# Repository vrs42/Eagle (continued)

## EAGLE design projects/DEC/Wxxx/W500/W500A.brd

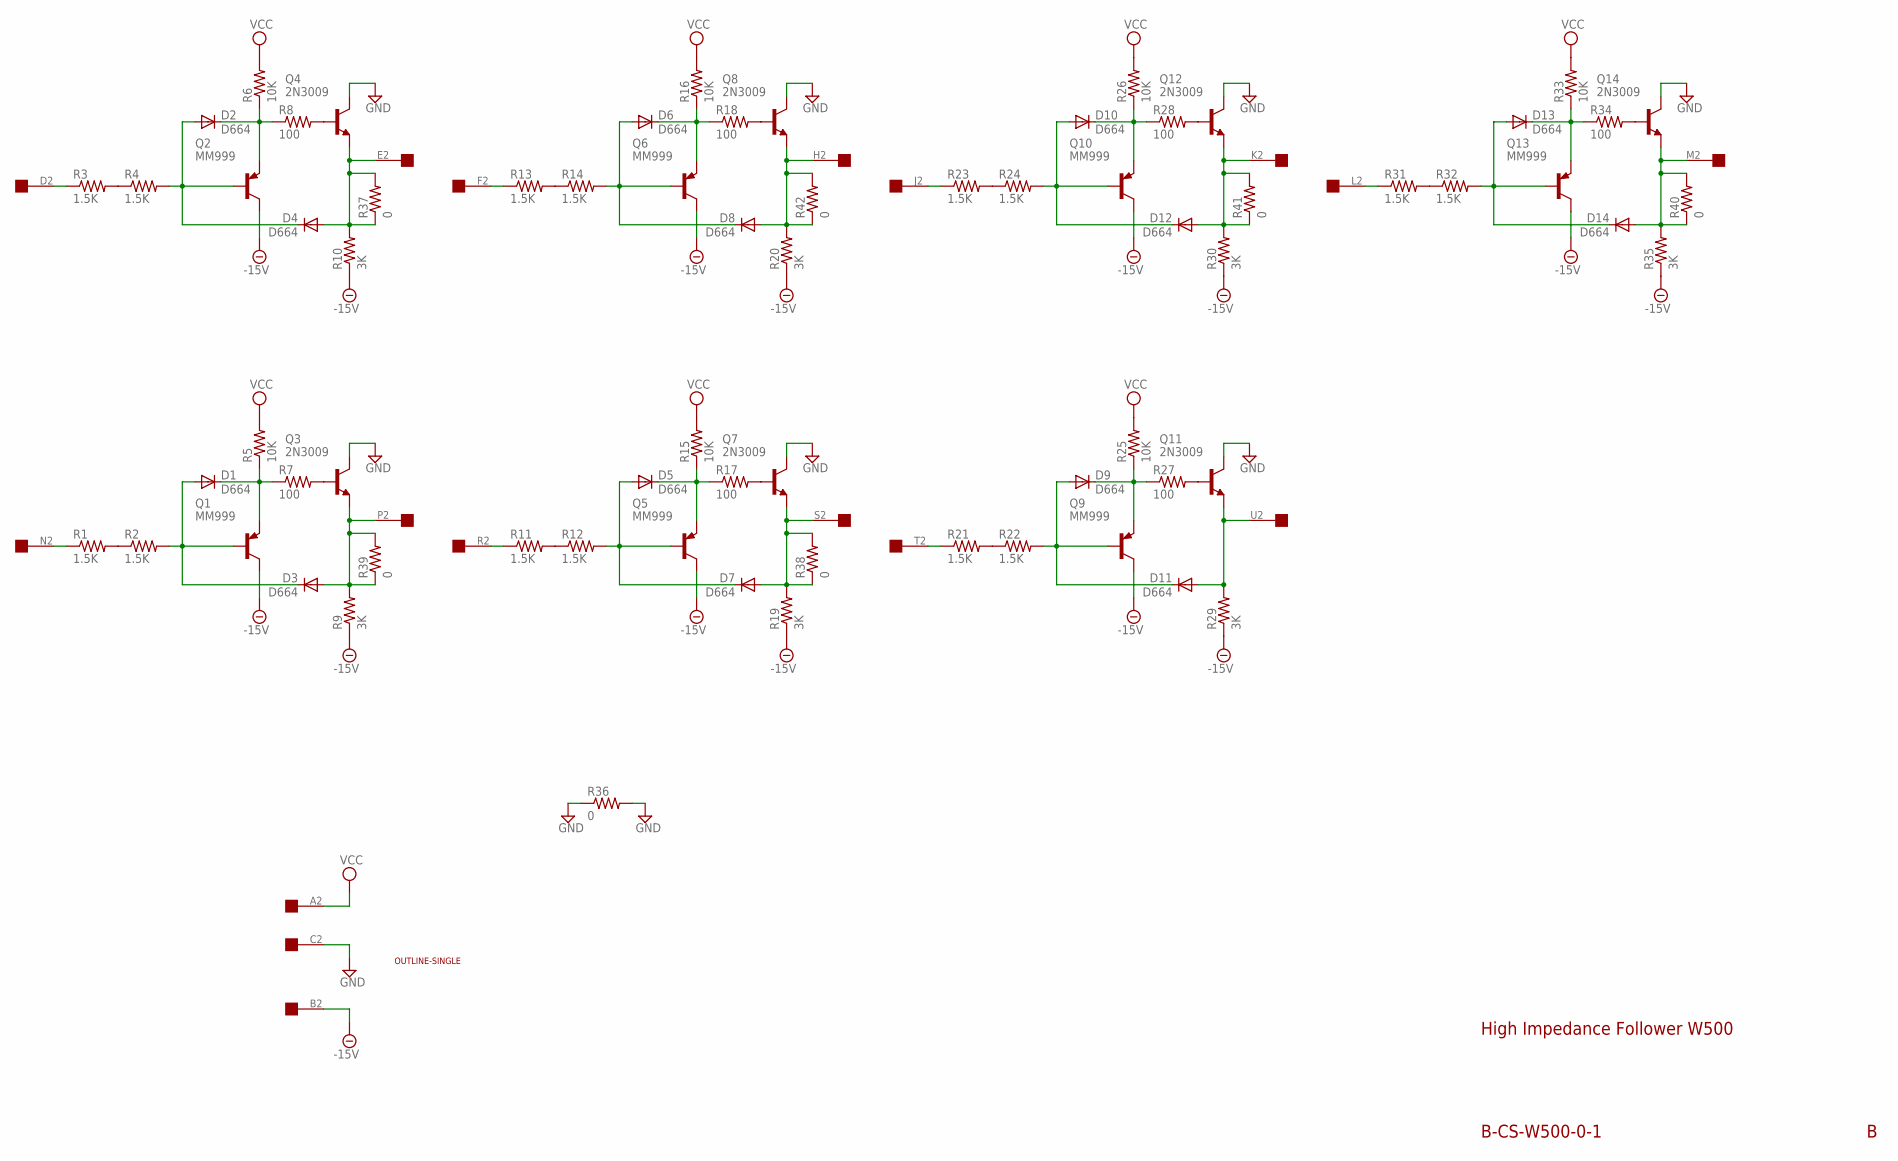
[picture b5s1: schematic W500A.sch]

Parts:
D1, D2, D3, D4, D5, D6, D7, D8, D9, D10, D11, D12, D13, D14: D664; DO35-10
Q1, Q2, Q5, Q6, Q9, Q10, Q13: MM999; TO5
Q3, Q4, Q7, Q8, Q11, Q12, Q14: 2N3009; TO5
R1, R2, R3, R4, R11, R12, R13, R14, R21, R22, R23, R24, R31, R32: 1.5K; 0207/10
R5, R6, R15, R16, R25, R26, R33: 10K; 0207/10
R7, R8, R17, R18, R27, R28, R34: 100; 0207/10
R9, R10, R19, R20, R29, R30, R35: 3K; 0207/10
R36, R37, R38, R39, R40, R41, R42: 0; 0207/10
U$1: OUTLINE-SINGLE; SINGLE
U$2: EDGE-1; EDGE-CON1

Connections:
-15V: Q1.3 (C), Q2.3 (C), Q5.3 (C), Q6.3 (C), Q9.3 (C), Q10.3 (C), Q13.3 (C), R9.1, R10.1, R19.1, R20.1, R29.1, R30.1, R35.1, U$2.B2
GND: Q3.3 (C), Q4.3 (C), Q7.3 (C), Q8.3 (C), Q11.3 (C), Q12.3 (C), Q14.3 (C), R36.1, R36.2, U$2.C2
unnamed: D2.C, Q2.1 (E), R6.1, R8.1
unnamed: D2.A, D4.C, Q2.2 (B), R4.2
unnamed: R3.2, R4.1
unnamed: R3.1, U$2.D2
unnamed: Q4.2 (B), R8.2
unnamed: D4.A, Q4.1 (E), R10.2, R37.1, R37.2, U$2.E2
unnamed: R1.2, R2.1
unnamed: R1.1, U$2.N2
unnamed: D1.A, D3.C, Q1.2 (B), R2.2
unnamed: D1.C, Q1.1 (E), R5.1, R7.1
unnamed: D3.A, Q3.1 (E), R9.2, R39.1, R39.2, U$2.P2
unnamed: Q3.2 (B), R7.2
unnamed: D6.C, Q6.1 (E), R16.1, R18.1
unnamed: D6.A, D8.C, Q6.2 (B), R14.2
unnamed: R13.2, R14.1
unnamed: R13.1, U$2.F2
unnamed: Q8.2 (B), R18.2
unnamed: D8.A, Q8.1 (E), R20.2, R42.1, R42.2, U$2.H2
unnamed: R11.2, R12.1
unnamed: R11.1, U$2.R2
unnamed: D5.A, D7.C, Q5.2 (B), R12.2
unnamed: D5.C, Q5.1 (E), R15.1, R17.1
unnamed: D7.A, Q7.1 (E), R19.2, R38.1, R38.2, U$2.S2
unnamed: Q7.2 (B), R17.2
unnamed: D10.C, Q10.1 (E), R26.1, R28.1
unnamed: D10.A, D12.C, Q10.2 (B), R24.2
unnamed: R23.2, R24.1
unnamed: R23.1, U$2.J2
unnamed: Q12.2 (B), R28.2
unnamed: D12.A, Q12.1 (E), R30.2, R41.1, R41.2, U$2.K2
unnamed: R21.2, R22.1
unnamed: D9.A, D11.C, Q9.2 (B), R22.2
unnamed: D9.C, Q9.1 (E), R25.1, R27.1
unnamed: D11.A, Q11.1 (E), R29.2, U$2.U2
unnamed: Q11.2 (B), R27.2
unnamed: R21.1, U$2.T2
unnamed: R31.2, R32.1
unnamed: R31.1, U$2.L2
unnamed: D13.A, D14.C, Q13.2 (B), R32.2
unnamed: D13.C, Q13.1 (E), R33.1, R34.1
unnamed: D14.A, Q14.1 (E), R35.2, R40.1, R40.2, U$2.M2
unnamed: Q14.2 (B), R34.2
VCC: R5.2, R6.2, R15.2, R16.2, R25.2, R26.2, R33.2, U$2.A2

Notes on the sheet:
B-CS-W500-0-1
High Impedance Follower W500

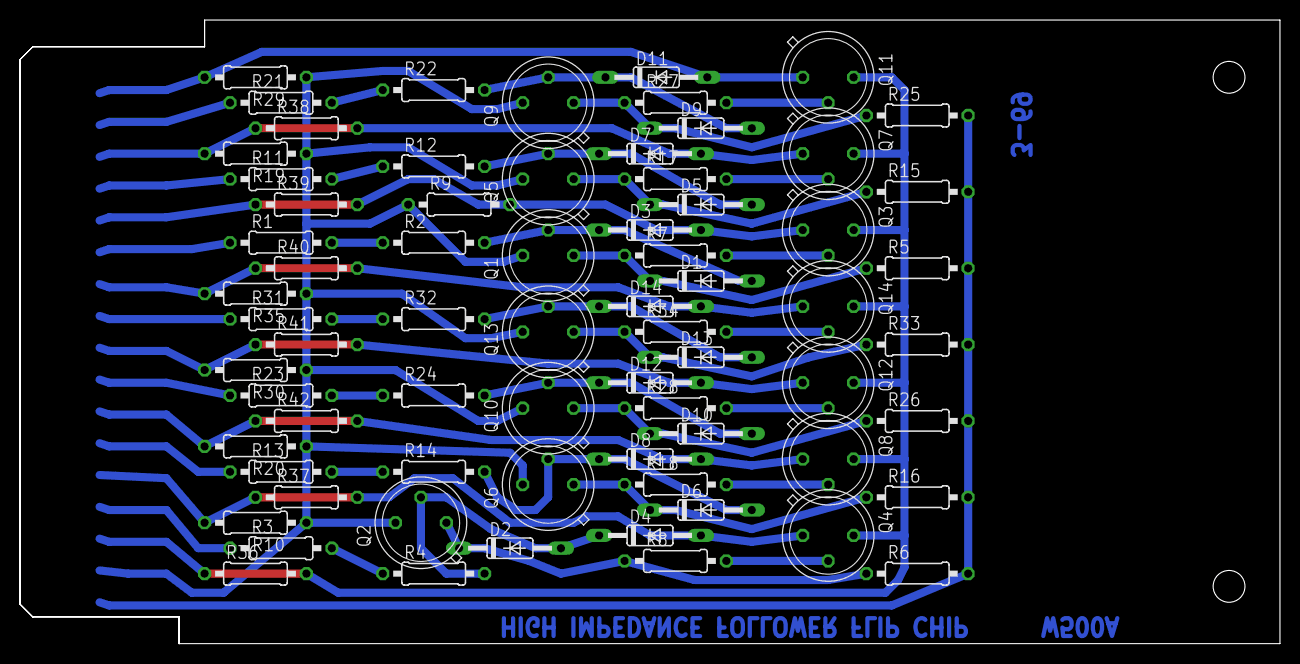
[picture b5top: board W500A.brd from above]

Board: 2 copper layers, 125.7 x 62.2 mm, 72 parts (0 on the bottom side), 45 nets.
